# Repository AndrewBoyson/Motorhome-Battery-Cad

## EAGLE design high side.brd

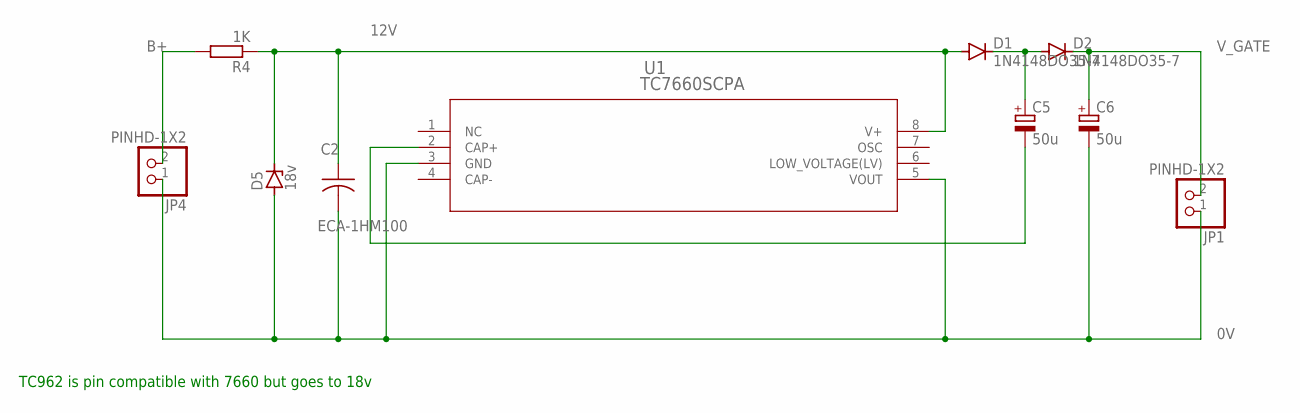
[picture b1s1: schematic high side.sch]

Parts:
C2: ECA-1HM100; CAP_RADIAL_2MM
C5, C6: 50u; CAPPRD508W65D1000H1100B
D1, D2: 1N4148DO35-7; DO35-7
D5: 18v; F126Z10
JP1, JP4: PINHD-1X2; 1X02
R4: 1K; 0204/7
U1: TC7660SCPA; PDIP8_300MC_MCH

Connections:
0V: C2.2, C6.2 (-), D5.A, JP1.1, JP4.1, U1.3 (GND), U1.5 (VOUT)
12V: C2.1, D1.A, D5.C, R4.1, U1.8 (V+)
B+: JP4.2, R4.2
unnamed: C5.2 (-), U1.2 (CAP+)
unnamed: C5.1 (+), D1.C, D2.A
V_GATE: C6.1 (+), D2.C, JP1.2

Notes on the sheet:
TC962 is pin compatible with 7660 but goes to 18v

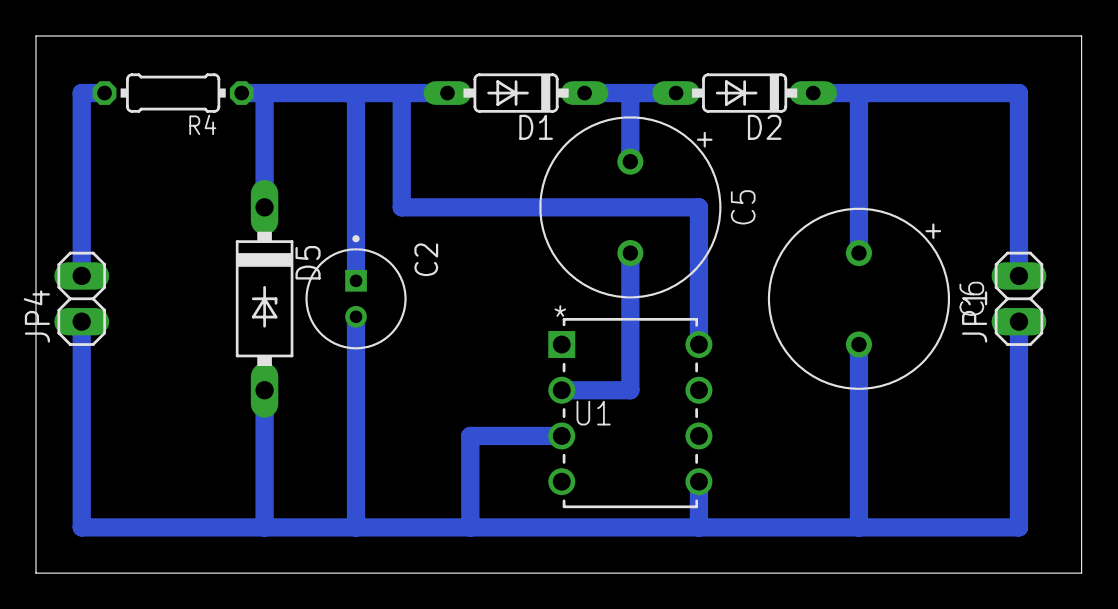
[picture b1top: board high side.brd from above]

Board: 2 copper layers, 58.1 x 29.8 mm, 10 parts (0 on the bottom side), 6 nets.

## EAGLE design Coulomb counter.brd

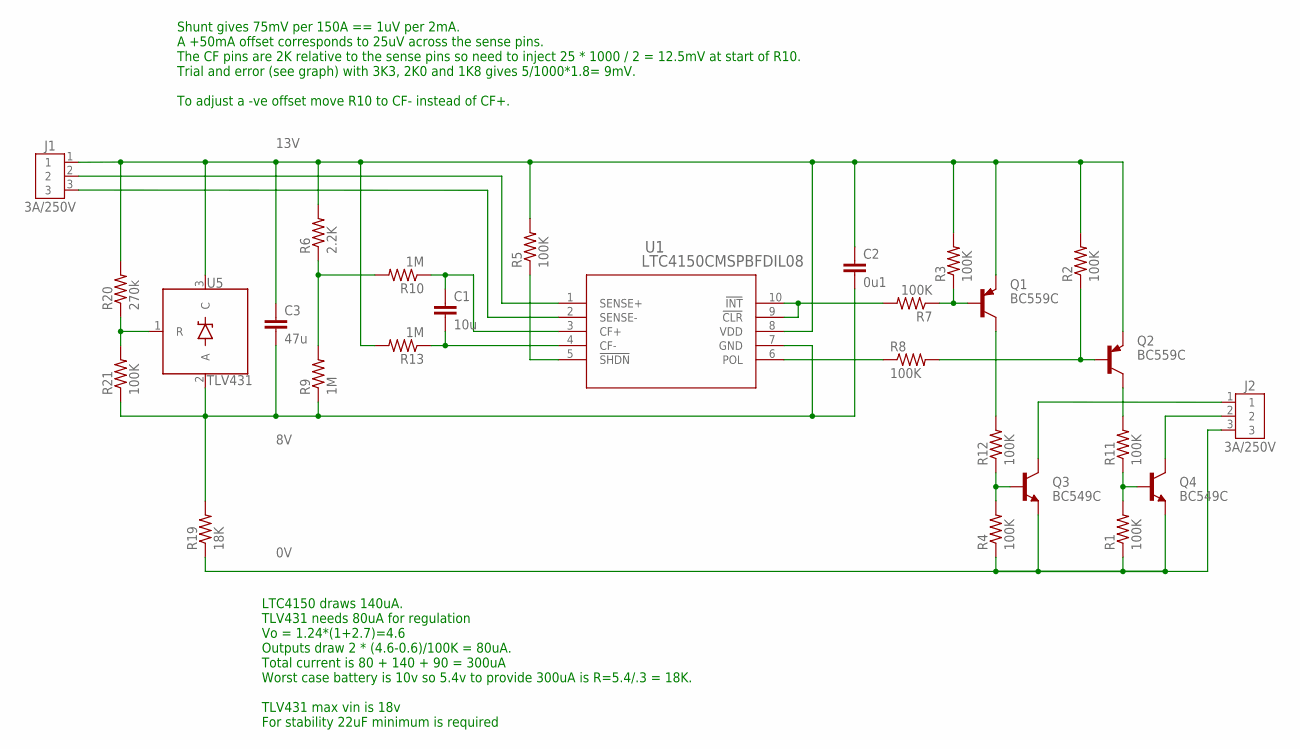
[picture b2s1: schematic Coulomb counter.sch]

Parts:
C1: 10u; C2.5-2
C2: 0u1; C2.5-2
C3: 47u; C2.5-2
J1, J2: 3A/250V; B3B-XH-A
Q1, Q2: BC559C; TO92-EBC
Q3, Q4: BC549C; TO92-EBC
R1, R2, R3, R4, R5, R7, R8, R11, R12, R21: 100K; 0204/7
R6: 2.2K; 0204/7
R9, R10, R13: 1M; 0204/7
R19: 18K; 0204/7
R20: 270k; 0204/7
U1: LTC4150CMSPBFDIL08; DIL10
U5: TLV431; TO92

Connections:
0V: J2.3, Q3.E, Q4.E, R1.1, R4.1, R19.1
8V: C2.2, C3.2, R9.1, R19.2, R21.1, U1.7 (GND), U5.2 (A)
13V: C2.1, C3.1, J1.1, Q1.E, Q2.E, R2.2, R3.2, R5.2, R6.2, R13.2, R20.2, U1.8 (VDD), U5.3 (C)
unnamed: J2.1, Q3.C
unnamed: R8.1, U1.6 (POL)
unnamed: R5.1, U1.5 (!SHDN)
unnamed: C1.2, R13.1, U1.4 (CF-)
unnamed: J1.3, U1.2 (SENSE-)
unnamed: R6.1, R9.2, R10.2
unnamed: J2.2, Q4.C
unnamed: C1.1, R10.1, U1.3 (CF+)
unnamed: Q1.B, R3.1, R7.1
unnamed: Q2.B, R2.1, R8.2
unnamed: Q2.C, R11.2
unnamed: Q1.C, R12.2
unnamed: Q3.B, R4.2, R12.1
unnamed: Q4.B, R1.2, R11.1
unnamed: R7.2, U1.9 (!CLR), U1.10 (!INT)
unnamed: R20.1, R21.2, U5.1 (R)
S+: J1.2, U1.1 (SENSE+)

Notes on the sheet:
LTC4150 draws 140uA. TLV431 needs 80uA for regulation Vo = 1.24*(1+2.7)=4.6 Outputs draw 2 * (4.6-0.6)/100K = 80uA. Total current is 80 + 140 + 90 = 300uA Worst case battery is 10v so 5.4v to provide 300uA is R=5.4/.3 = 18K. TLV431 max vin is 18v For stability 22uF minimum is required
Shunt gives 75mV per 150A == 1uV per 2mA. A +50mA offset corresponds to 25uV across the sense pins. The CF pins are 2K relative to the sense pins so need to inject 25 * 1000 / 2 = 12.5mV at start of R10. Trial and error (see graph) with 3K3, 2K0 and 1K8 gives 5/1000*1.8= 9mV. To adjust a -ve offset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

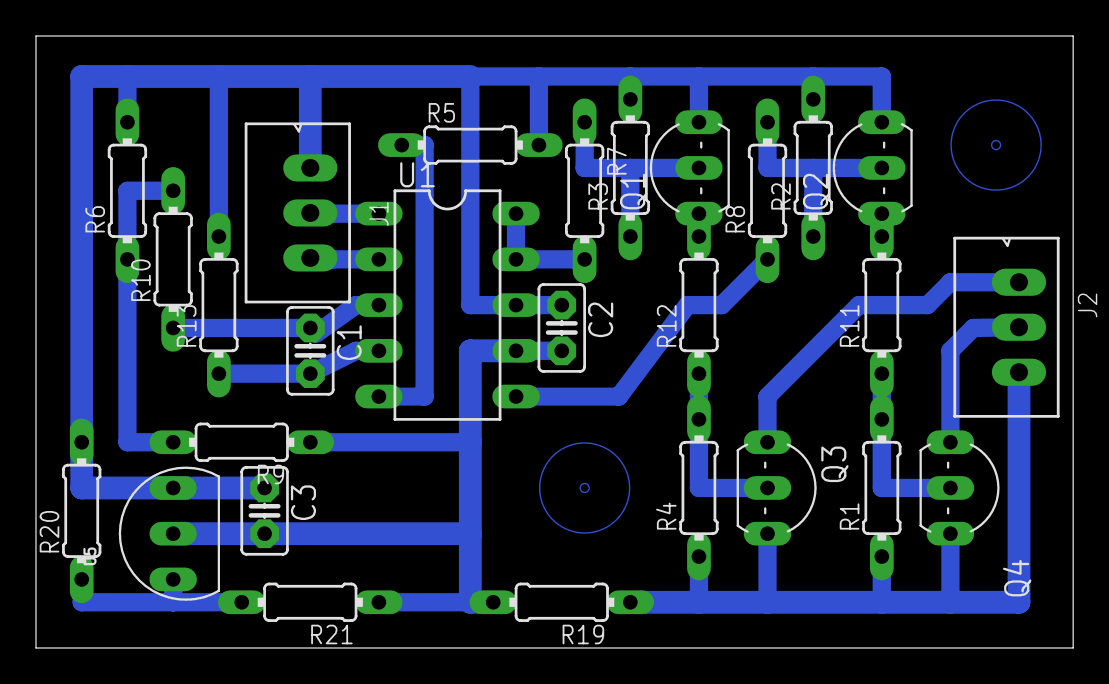
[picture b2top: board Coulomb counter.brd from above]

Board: 2 copper layers, 57.6 x 34.0 mm, 27 parts (0 on the bottom side), 20 nets.

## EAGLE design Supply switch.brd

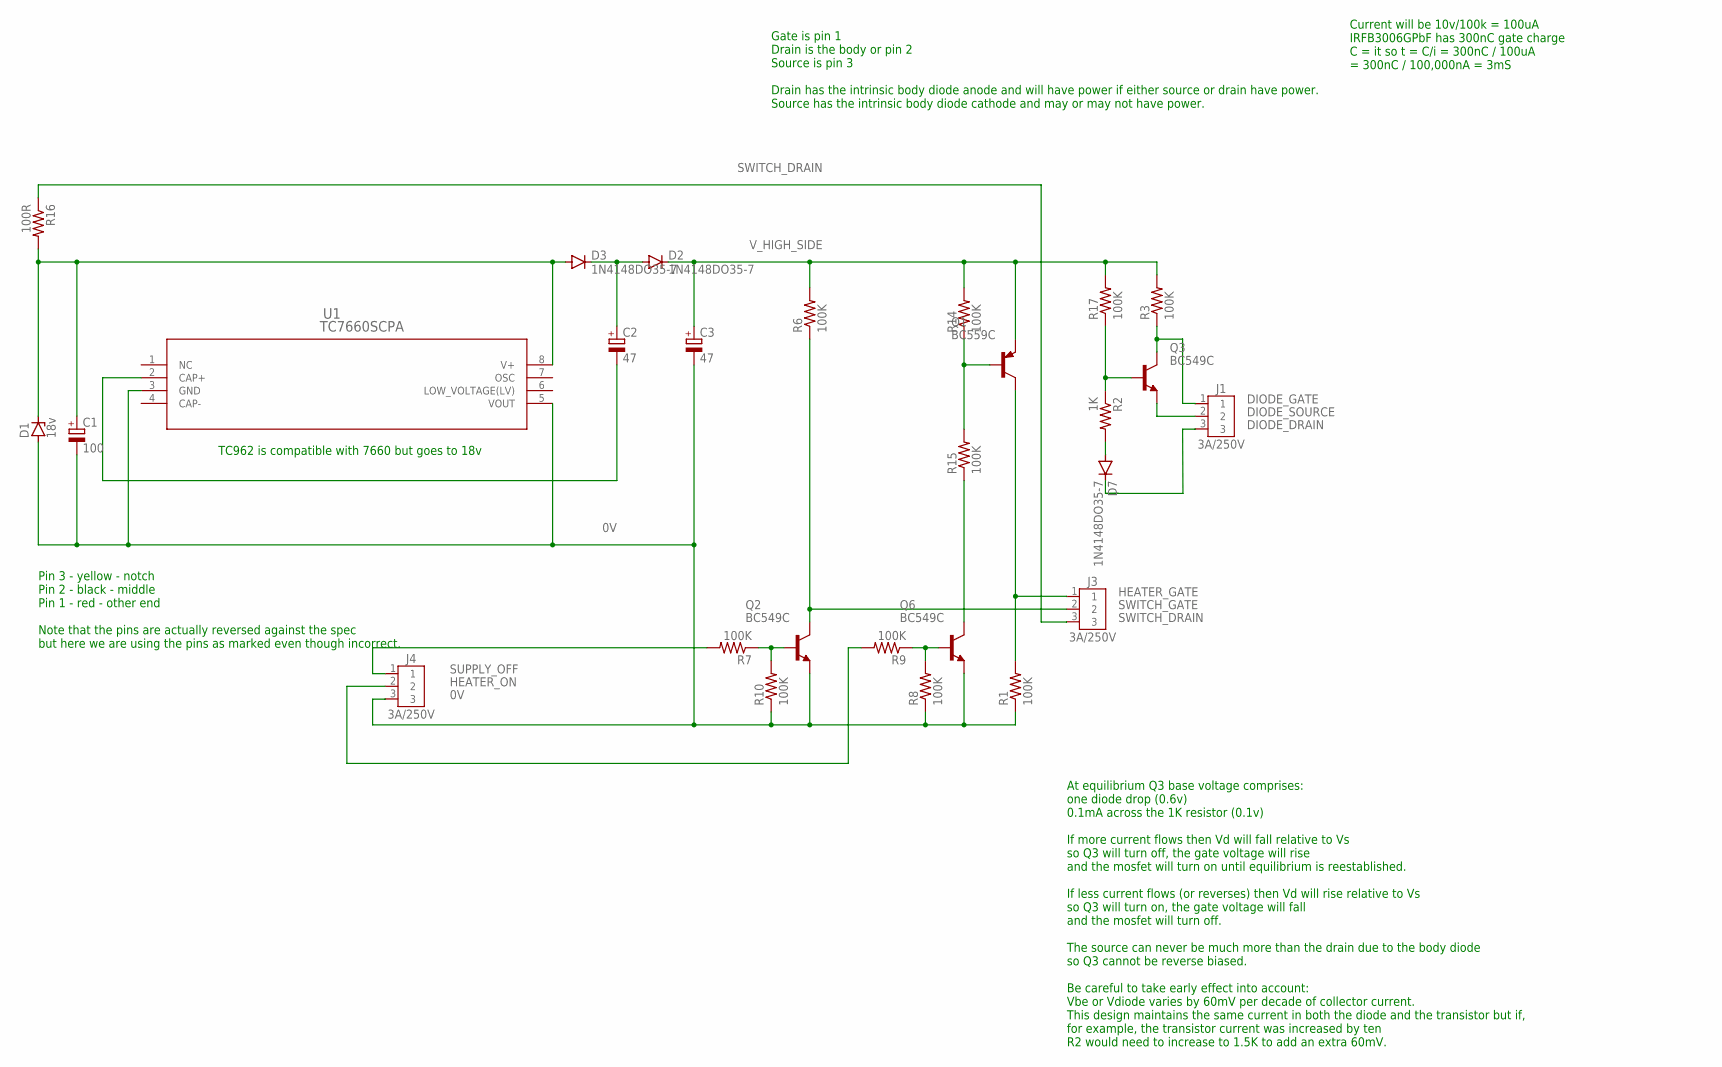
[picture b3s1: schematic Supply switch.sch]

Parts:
C1: 100; CAPPRD508W65D1000H1100B
C2, C3: 47; CAPPRD508W65D1000H1100B
D1: 18v; F126Z10
D2, D3, D7: 1N4148DO35-7; DO35-7
J1, J3, J4: 3A/250V; B3B-XH-A
Q1: BC559C; TO92-EBC
Q2, Q3, Q6: BC549C; TO92-EBC
R1, R3, R6, R7, R8, R9, R10, R14, R15, R17: 100K; 0204/7
R2: 1K; 0204/7
R16: 100R; 0204/7
U1: TC7660SCPA; PDIP8_300MC_MCH

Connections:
0V: C1.2 (-), C3.2 (-), D1.A, J4.3, Q2.E, Q6.E, R1.1, R8.1, R10.1, U1.3 (GND), U1.5 (VOUT)
DIODE_DRAIN: D7.C, J1.3
DIODE_GATE: J1.1, Q3.C, R3.1
DIODE_SOURCE: J1.2, Q3.E
HEATER_GATE: J3.1, Q1.C, R1.2
HEATER_ON: J4.2, R9.2
unnamed: D7.A, R2.2
unnamed: Q1.B, R14.1, R15.2
unnamed: Q6.C, R15.1
unnamed: Q2.B, R7.1, R10.2
unnamed: Q3.B, R2.1, R17.1
unnamed: Q6.B, R8.2, R9.1
unnamed: C1.1 (+), D1.C, D3.A, R16.2, U1.8 (V+)
unnamed: C2.2 (-), U1.2 (CAP+)
unnamed: C2.1 (+), D2.A, D3.C
SUPPLY_OFF: J4.1, R7.2
SWITCH_DRAIN: J3.3, R16.1
SWITCH_GATE: J3.2, Q2.C, R6.1
V_HIGH_SIDE: C3.1 (+), D2.C, Q1.E, R3.2, R6.2, R14.2, R17.2

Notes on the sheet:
Gate is pin 1 Drain is the body or pin 2 Source is pin 3 Drain has the intrinsic body diode anode and will have power if either source or drain have power. Source has the intrinsic body diode cathode and may or may not have power.
Current will be 10v/100k = 100uA IRFB3006GPbF has 300nC gate charge C = it so t = C/i = 300nC / 100uA = 300nC / 100,000nA = 3mS
TC962 is compatible with 7660 but goes to 18v
Pin 3 - yellow - notch Pin 2 - black - middle Pin 1 - red - other end Note that the pins are actually reversed against the spec but here we are using the pins as marked even though incorrect.
At equilibrium Q3 base voltage comprises: one diode drop (0.6v) 0.1mA across the 1K resistor (0.1v) If more current flows then Vd will fall relative to Vs so Q3 will turn off, the gate voltage will rise and the mosfet will turn on until equilibrium is reestablished. If less current flows (or revers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

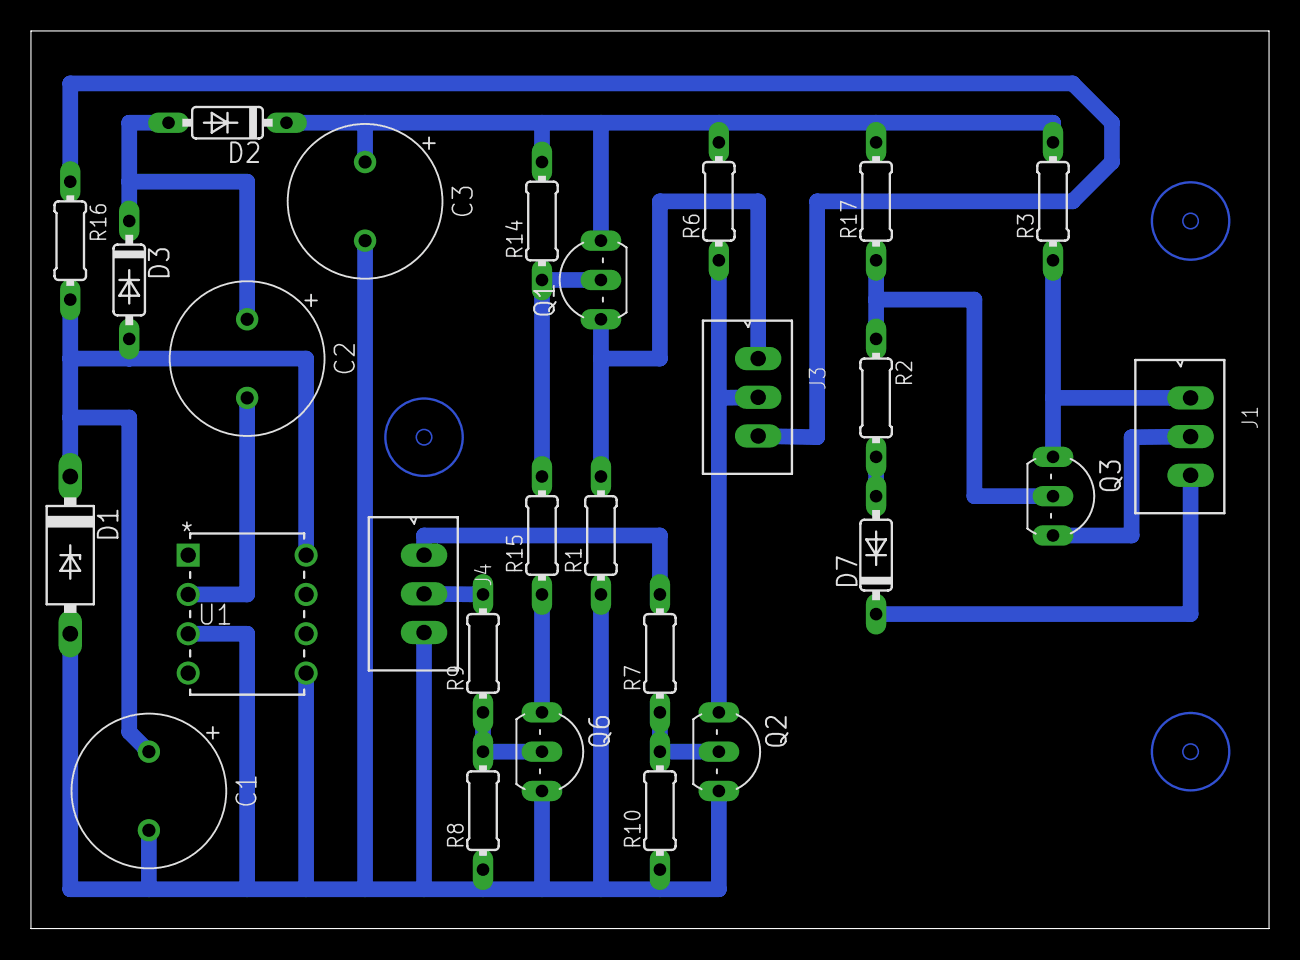
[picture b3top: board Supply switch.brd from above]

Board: 2 copper layers, 80.0 x 58.0 mm, 27 parts (0 on the bottom side), 19 nets.

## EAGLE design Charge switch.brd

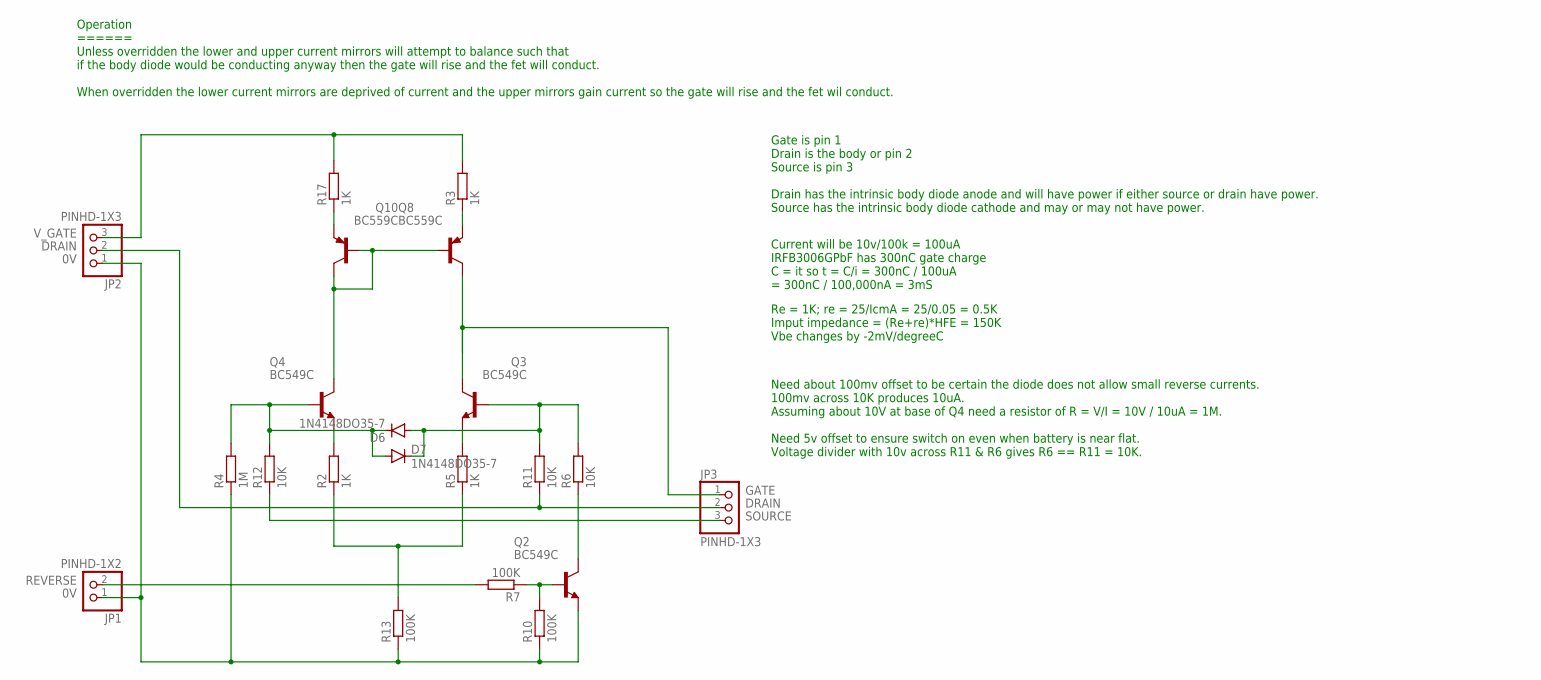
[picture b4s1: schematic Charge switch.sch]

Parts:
D6, D7: 1N4148DO35-7; DO35-7
JP1: PINHD-1X2; 1X02
JP2, JP3: PINHD-1X3; 1X03
Q2, Q3, Q4: BC549C; TO92-EBC
Q8, Q10: BC559C; TO92-EBC
R2, R3, R5, R17: 1K; 0204/7
R4: 1M; 0204/7
R6, R11, R12: 10K; 0204/7
R7, R10, R13: 100K; 0204/7

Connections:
0V: JP1.1, JP2.1, Q2.E, R4.1, R10.1, R13.1
DRAIN: JP2.2, JP3.2, R11.1
GATE: JP3.1, Q3.C, Q8.C
unnamed: Q4.C, Q8.B, Q10.B, Q10.C
unnamed: R2.1, R5.1, R13.2
unnamed: Q2.B, R7.1, R10.2
unnamed: D6.A, D7.C, Q3.B, R6.2, R11.2
unnamed: D6.C, D7.A, Q4.B, R4.2, R12.2
unnamed: Q4.E, R2.2
unnamed: Q2.C, R6.1
unnamed: Q3.E, R5.2
unnamed: Q10.E, R17.1
unnamed: Q8.E, R3.1
REVERSE: JP1.2, R7.2
SOURCE: JP3.3, R12.1
V_GATE: JP2.3, R3.2, R17.2

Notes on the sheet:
Gate is pin 1 Drain is the body or pin 2 Source is pin 3 Drain has the intrinsic body diode anode and will have power if either source or drain have power. Source has the intrinsic body diode cathode and may or may not have power.
Operation ====== Unless overridden the lower and upper current mirrors will attempt to balance such that if the body diode would be conducting anyway then the gate will rise and the fet will conduct. When overridden the lower current mirrors are deprived of current and the upper mirrors gain curren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
Current will be 10v/100k = 100uA IRFB3006GPbF has 300nC gate charge C = it so t = C/i = 300nC / 100uA = 300nC / 100,000nA = 3mS
Need about 100mv offset to be certain the diode does not allow small reverse currents. 100mv across 10K produces 10uA. Assuming about 10V at base of Q4 need a resistor of R = V/I = 10V / 10uA = 1M. Need 5v offset to ensure switch on even when battery is near flat. Voltage divider with 10v across R1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
Re = 1K; re = 25/IcmA = 25/0.05 = 0.5K Imput impedance = (Re+re)*HFE = 150K Vbe changes by -2mV/degreeC

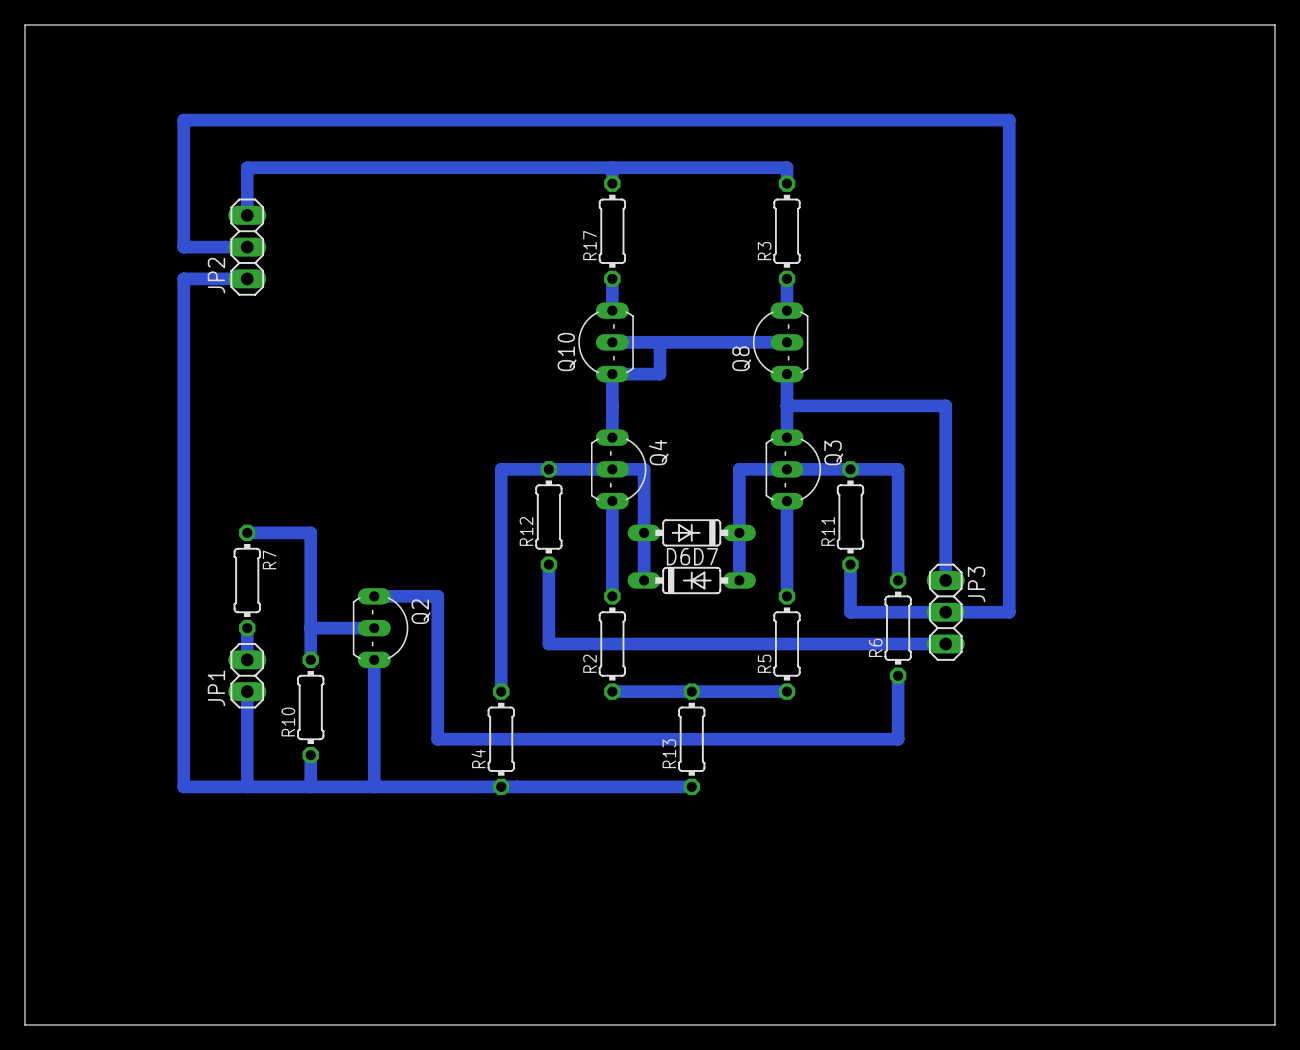
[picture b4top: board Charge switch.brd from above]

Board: 2 copper layers, 100.0 x 80.0 mm, 21 parts (0 on the bottom side), 16 nets.

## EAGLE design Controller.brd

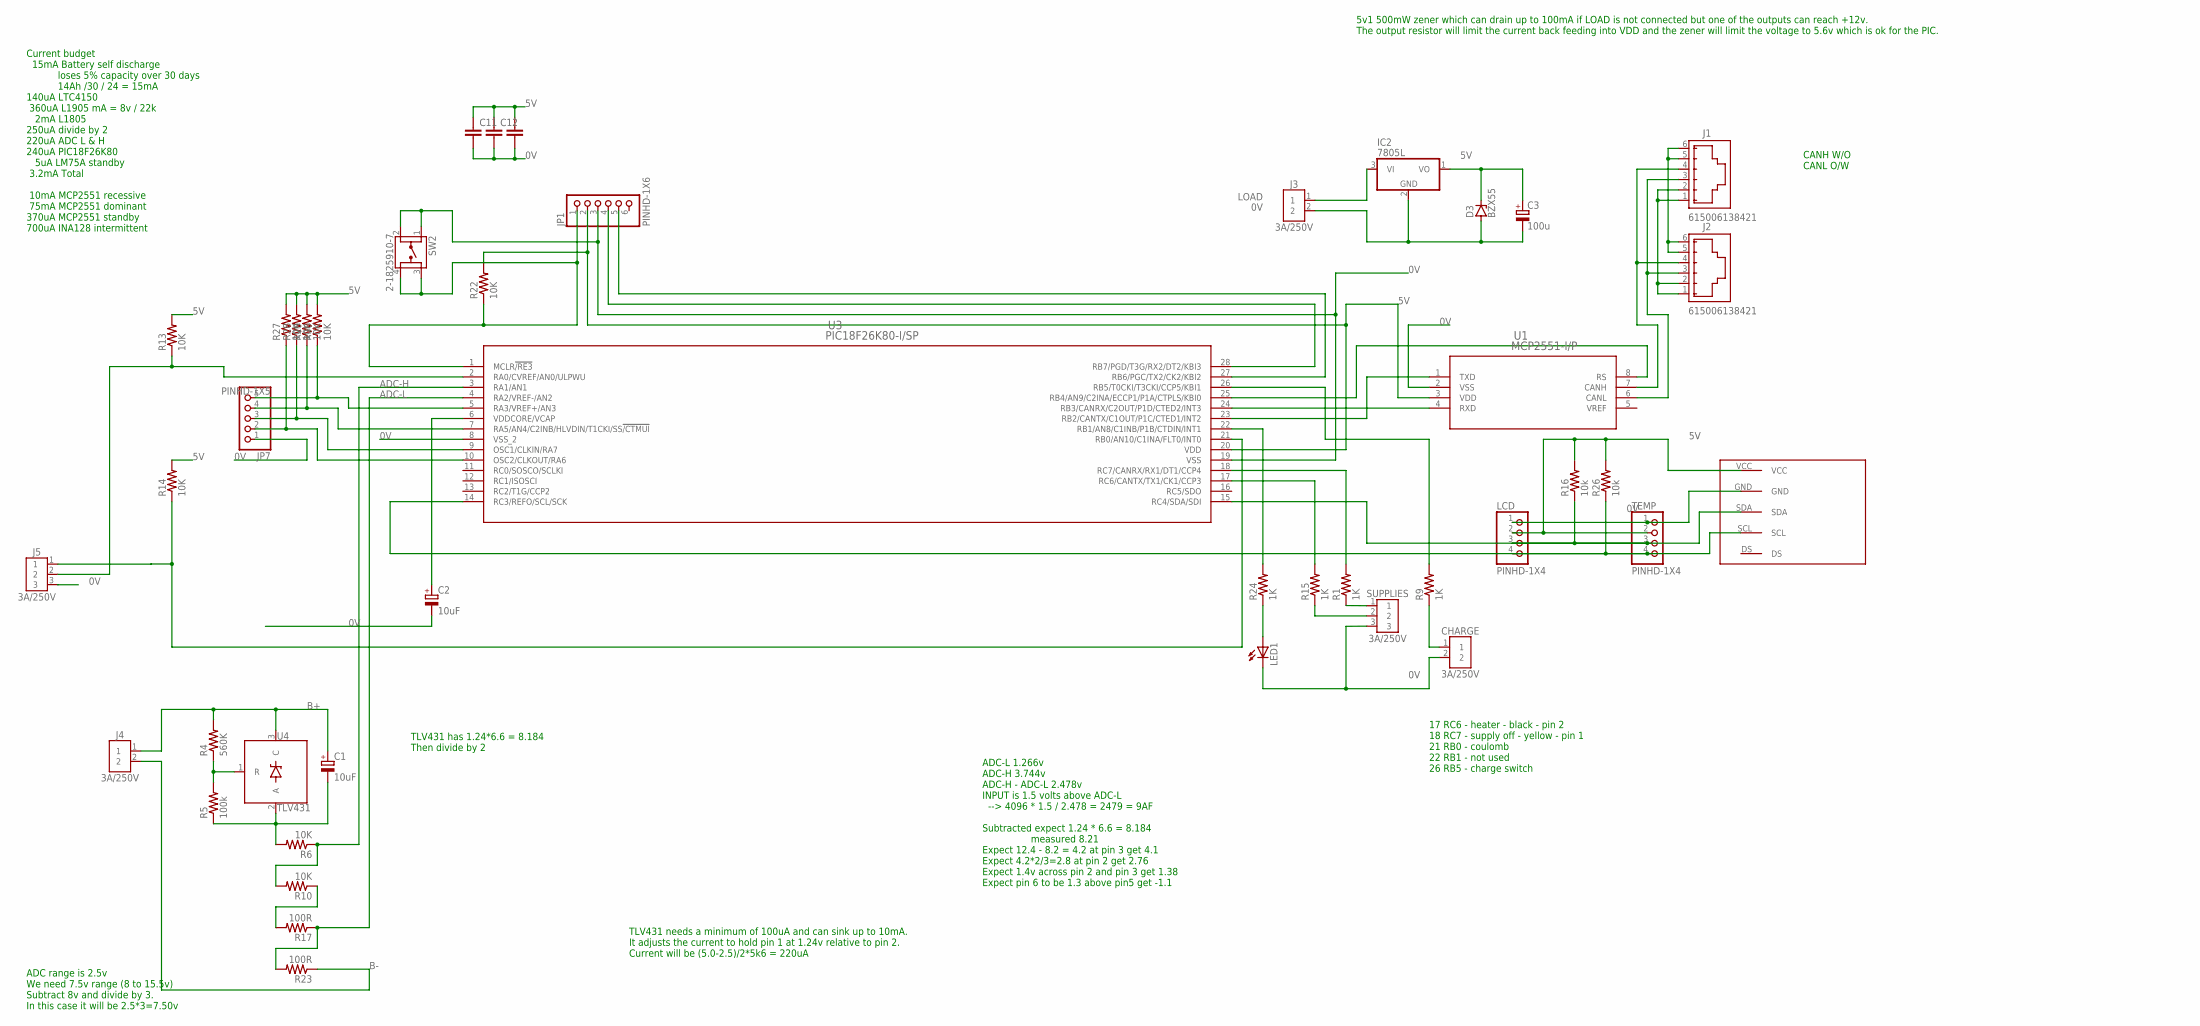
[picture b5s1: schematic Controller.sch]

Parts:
C1, C2: 10uF; E3,5-8
C3: 100u; E3,5-8
C7, C11, C12: C2,5-3; C2.5-3
CHARGE: 3A/250V; B2B-XH-A
D3: BZX55; DO35Z10
IC2: 7805L; TO92
J1, J2: 615006138421
J3, J4: 3A/250V; B2B-XH-A
J5: 3A/250V; B3B-XH-A
JP1: PINHD-1X6; 1X06
JP7: PINHD-1X5; 1X05
LCD: PINHD-1X4; 1X04
LED1: LED3MM
R1, R9, R15, R24: 1K; 0204/7
R4: 560K; 0204/7
R5: 100k; 0204/7
R6, R10, R13, R14, R22: 10K; 0204/7
R16, R26: 10k; 0204/7
R17, R23: 100R; 0204/7
R27, R28, R29, R30: 10K; 0204/7-90
SUPPLIES: 3A/250V; B3B-XH-A
SW2: 2-1825910-7
TEMP: PINHD-1X4; 1X04
U1: MCP2551-I/P; PDIP8_300MC_MCH
U3: PIC18F26K80-I/SP; SPDIP28_300MC_MCH
U4: TLV431; TO92
U$1: LM75

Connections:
0V: C2.-, C3.-, C7.2, C11.2, C12.2, CHARGE.2, D3.A, IC2.2 (GND), J3.2, J5.3, JP1.3, JP7.1, LCD.1, LED1.K (C), SUPPLIES.3, SW2.1, SW2.2, TEMP.1, U1.2 (VSS), U3.8 (VSS_2), U3.19 (VSS), U$1.GND
5V: C3.+, C7.1, C11.1, C12.1, D3.C, IC2.1 (VO), JP1.2, LCD.2, R13.2, R14.2, R16.2, R22.2, R26.2, R27.2, R28.2, R29.2, R30.2, TEMP.2, U1.3 (VDD), U3.20 (VDD), U$1.VCC
ADC-H: R6.1, R10.2, U3.3 (RA1/AN1)
ADC-L: R17.1, R23.2, U3.4 (RA2/VREF-/AN2)
B+: C1.+, J4.1, R4.2, U4.3 (C)
B-: J4.2, R23.1
LCD: LCD.3, R16.1, TEMP.3, U3.15 (RC4/SDA/SDI), U$1.SDA
LOAD: IC2.3 (VI), J3.1
unnamed: U1.4 (RXD), U3.24 (RB3/CANRX/C2OUT/P1D/CTED2/INT3)
unnamed: U1.1 (TXD), U3.23 (RB2/CANTX/C1OUT/P1C/CTED1/INT2)
unnamed: R1.2, U3.18 (RC7/CANRX/RX1/DT1/CCP4)
unnamed: J1.3, J2.3, U1.6 (CANL)
unnamed: JP1.1, R22.1, SW2.3, SW2.4, U3.1 (MCLR!/RE3)
unnamed: LCD.4, R26.1, TEMP.4, U3.14 (RC3/REFO/SCL/SCK), U$1.SCL
unnamed: JP1.4, U3.28 (RB7/PGD/T3G/RX2/DT2/KBI3)
unnamed: JP1.5, U3.27 (RB6/PGC/TX2/CK2/KBI2)
unnamed: C1.-, R5.1, R6.2, U4.2 (A)
unnamed: R1.1, SUPPLIES.1
unnamed: R24.2, U3.22 (RB1/AN8/C1INB/P1B/CTDIN/INT1)
unnamed: R10.1, R17.2
unnamed: C2.+, U3.6 (VDDCORE/VCAP)
unnamed: CHARGE.1, R9.1
unnamed: R4.1, R5.2, U4.1 (R)
unnamed: J5.1, R14.1, U3.21 (RB0/AN10/C1INA/FLT0/INT0)
unnamed: J5.2, R13.1, U3.2 (RA0/CVREF/AN0/ULPWU)
unnamed: R15.1, SUPPLIES.2
unnamed: J1.4, J2.4, U1.7 (CANH)
unnamed: R9.2, U3.26 (RB5/T0CKI/T3CKI/CCP5/KBI1)
unnamed: JP7.5, R30.1, U3.5 (RA3/VREF+/AN3)
unnamed: J1.5, J1.6, J2.5, J2.6
unnamed: J1.1, J1.2, J2.1, J2.2
unnamed: R15.2, U3.17 (RC6/CANTX/TX1/CK1/CCP3)
unnamed: JP7.4, R29.1, U3.7 (RA5/AN4/C2INB/HLVDIN/T1CKI/SS!/CTMUI)
unnamed: JP7.3, R28.1, U3.9 (OSC1/CLKIN/RA7)
unnamed: JP7.2, R27.1, U3.10 (OSC2/CLKOUT/RA6)
unnamed: LED1.A, R24.1
unnamed: U1.8 (RS), U3.25 (RB4/AN9/C2INA/ECCP1/P1A/CTPLS/KBI0)

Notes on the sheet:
ADC range is 2.5v We need 7.5v range (8 to 15.5v) Subtract 8v and divide by 3. In this case it will be 2.5*3=7.50v
TLV431 needs a minimum of 100uA and can sink up to 10mA. It adjusts the current to hold pin 1 at 1.24v relative to pin 2. Current will be (5.0-2.5)/2*5k6 = 220uA
Current budget 15mA Battery self discharge loses 5% capacity over 30 days 14Ah /30 / 24 = 15mA 140uA LTC4150 360uA L1905 mA = 8v / 22k 2mA L1805 250uA divide by 2 220uA ADC L & H 240uA PIC18F26K80 5uA LM75A standby 3.2mA Total 10mA MCP2551 recessive 75mA MCP2551 dominant 370uA MCP2551 standby 700uA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
5v1 500mW zener which can drain up to 100mA if LOAD is not connected but one of the outputs can reach +12v. The output resistor will limit the current back feeding into VDD and the zener will limit the voltage to 5.6v which is ok for the PIC.
ADC-L 1.266v ADC-H 3.744v ADC-H - ADC-L 2.478v INPUT is 1.5 volts above ADC-L --> 4096 * 1.5 / 2.478 = 2479 = 9AF Subtracted expect 1.24 * 6.6 = 8.184 measured 8.21 Expect 12.4 - 8.2 = 4.2 at pin 3 get 4.1 Expect 4.2*2/3=2.8 at pin 2 get 2.76 Expect 1.4v across pin 2 and pin 3 get 1.38 Expect pin 6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
17 RC6 - heater - black - pin 2 18 RC7 - supply off - yellow - pin 1 21 RB0 - coulomb 22 RB1 - not used 26 RB5 - charge switch
TLV431 has 1.24*6.6 = 8.184 Then divide by 2
CANH W/O CANL O/W

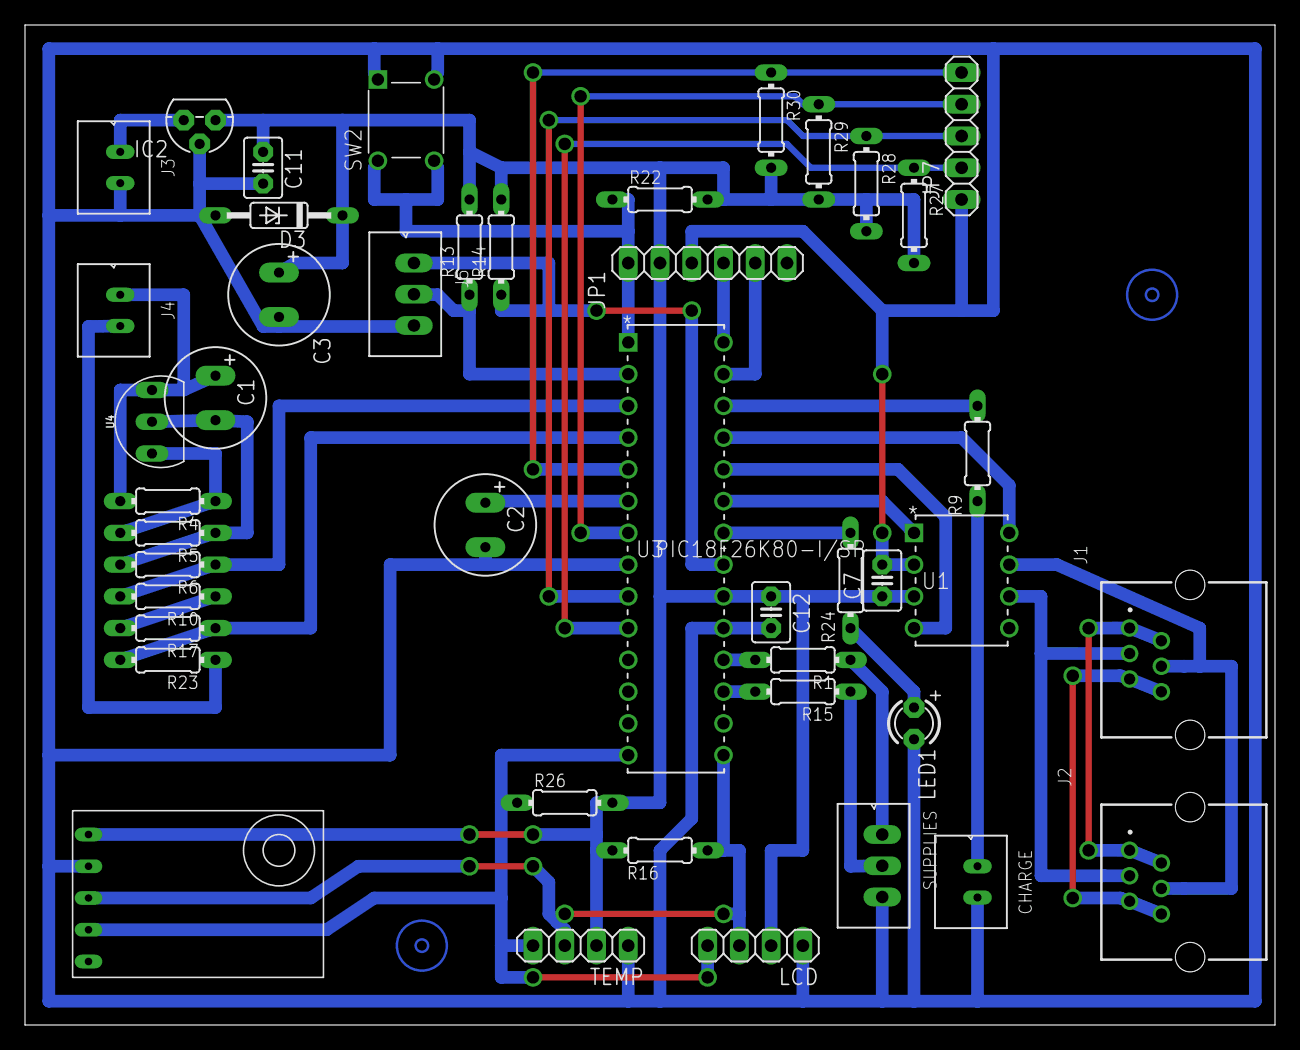
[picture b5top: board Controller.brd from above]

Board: 2 copper layers, 100.0 x 80.0 mm, 44 parts (0 on the bottom side), 37 nets.

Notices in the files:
parts and their libraries:
Wurth_Connectors_WR-MJ: Copyright: Würth Elektronik
COPYRIGHT: Copyright (C) 2021 Ultra Librarian. All rights reserved.
